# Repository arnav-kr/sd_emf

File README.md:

# SD EMF

A simple EMF detector built using discrete components with a SD Card shaped PCB.

## Schematic

## PCB

## BOM
| Part | Quantity |
| --- | --- |
| Battery Holder | 1 |
| LED | 1 |
| 2N3904 Transistor | 3 |
| Resistor 220 Ohm | 1 |
| Resistor 4.7k Ohm | 1 |
| Potentiometer | 2 |
| Push Button | 1 |

## License
This project is licensed under the [AGPL-3.0 License](LICENSE).

## Author
Made by [Arnav Kumar](https://github.com/arnav-kr) | Slack (`@ak`)

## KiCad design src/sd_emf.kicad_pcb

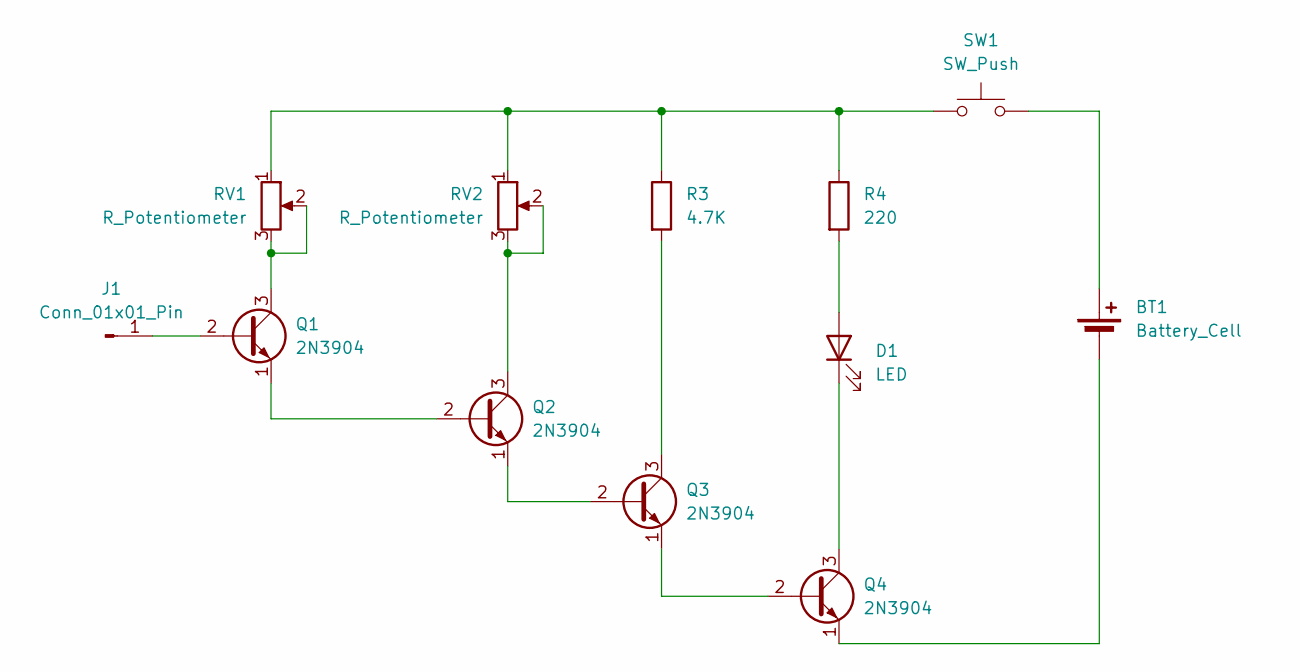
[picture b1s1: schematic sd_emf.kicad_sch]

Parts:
BT1: Battery_Cell; BatteryHolder_Keystone_3034_1x20mm
D1: LED; LED_D5.0mm
J1: Conn_01x01_Pin; PinHeader_1x01_P2.54mm_Vertical
Q1, Q2, Q3, Q4: 2N3904; TO-92_HandSolder
R3: 4.7K; R_Axial_DIN0207_L6.3mm_D2.5mm_P7.62mm_Horizontal
R4: 220; R_Axial_DIN0207_L6.3mm_D2.5mm_P7.62mm_Horizontal
RV1, RV2: R_Potentiometer; Potentiometer_Vishay_T73YP_Vertical
SW1: SW_Push; SW_PUSH_6mm

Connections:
unnamed: BT1.1 (+), SW1.2
unnamed: BT1.2 (-), Q4.1 (E)
unnamed: D1.2 (A), R4.2
unnamed: D1.1 (K), Q4.3 (C)
unnamed: J1.1, Q1.2 (B)
unnamed: Q1.3 (C), RV1.2, RV1.3
unnamed: Q1.1 (E), Q2.2 (B)
unnamed: Q2.3 (C), RV2.2, RV2.3
unnamed: Q2.1 (E), Q3.2 (B)
unnamed: Q3.3 (C), R3.2
unnamed: Q3.1 (E), Q4.2 (B)
unnamed: R3.1, R4.1, RV1.1, RV2.1, SW1.1

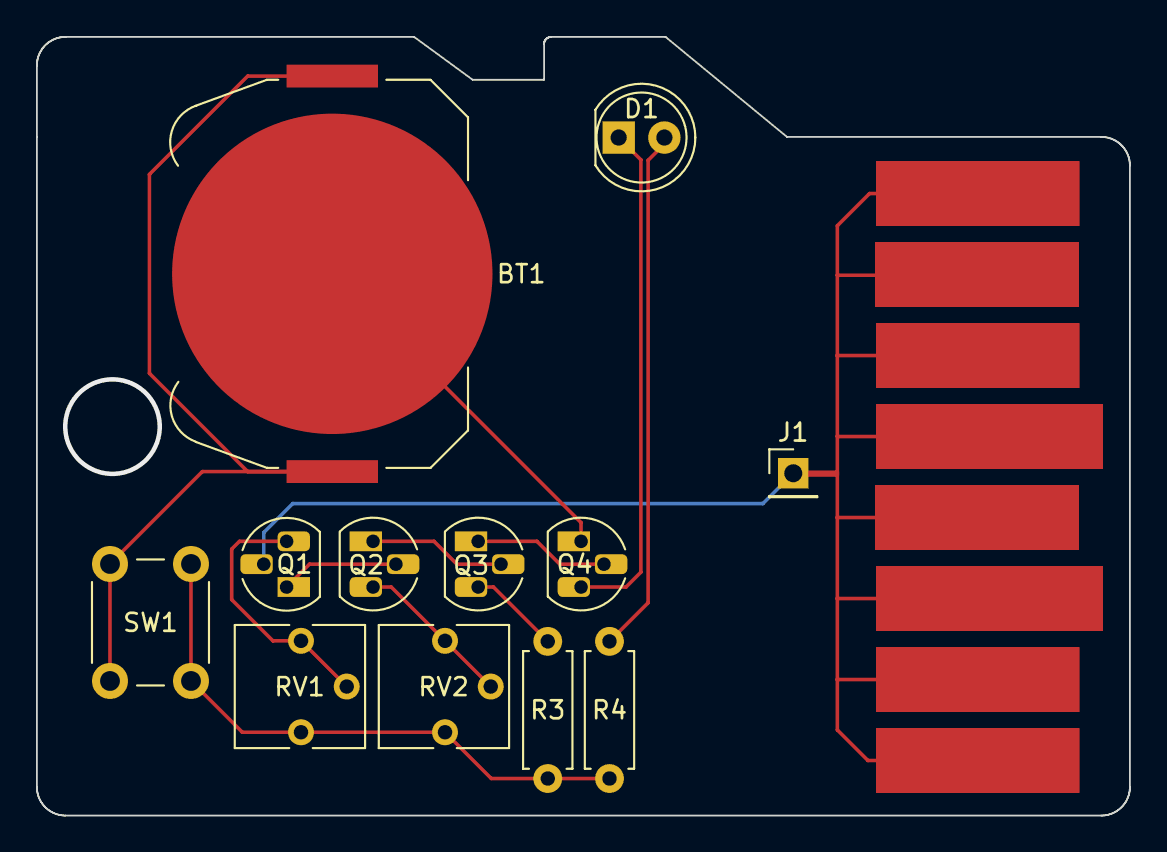
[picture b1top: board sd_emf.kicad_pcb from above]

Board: 2 copper layers, 60.7 x 43.3 mm, 12 parts (0 on the bottom side), 12 nets.

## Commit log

2025-06-28 docs: update readme, page setup
2025-06-28 feat: production files
2025-06-28 docs: update readme
2025-06-29 feat: update pcb
